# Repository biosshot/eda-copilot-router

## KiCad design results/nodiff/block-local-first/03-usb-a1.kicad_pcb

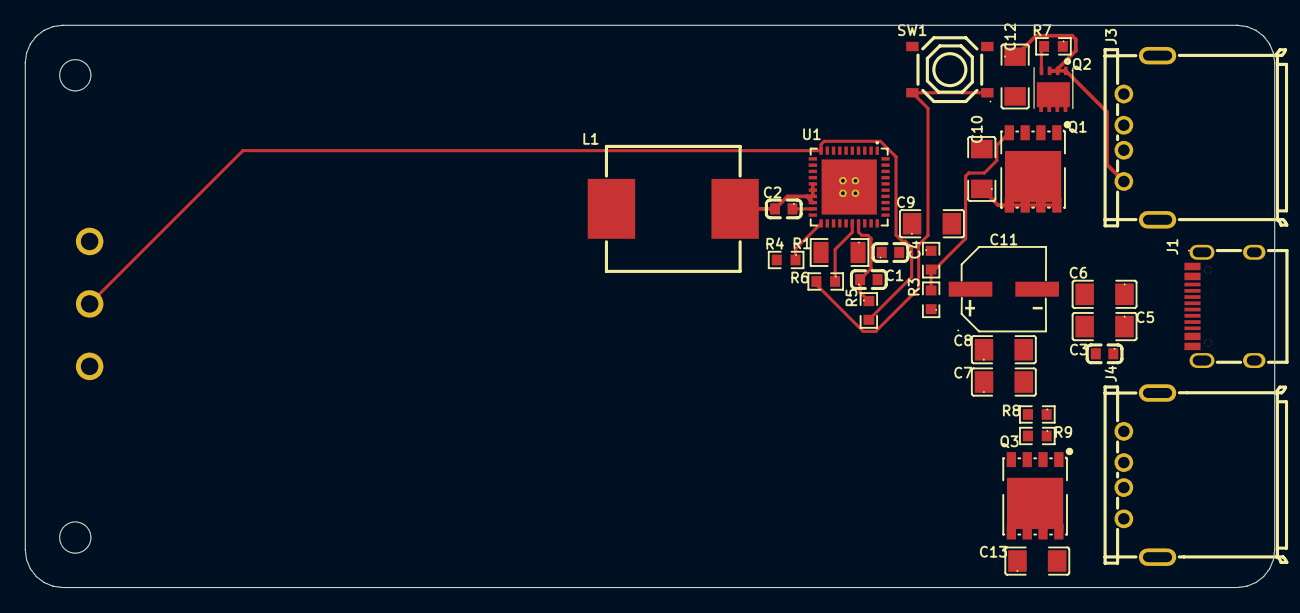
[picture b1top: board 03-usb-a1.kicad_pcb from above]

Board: 2 copper layers, 100.0 x 45.0 mm, 32 parts (1 on the bottom side), 28 nets.

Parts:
C1: 2.2uF; C23630_C0603
C2, C3, C4: 100nF; C14663_C0603
C5, C6, C7, C8, C9: 22uF; C12891_C1206
C10, C12, C13: 10uF; C14860_C1206
C11: 220uF; C51018389_CAP-SMD_BD6.3-L6.6-W6.6-LS7.3-FD_H7.7
J1: USB-C_PD_IN_OUT; C165948_USB-C_SMD-TYPE-C-31-M-12_1
J2: BATTERY_1S2P_10AH_PROTECTED_NTC; C474882_CONN-TH_3P-P5.00_KF301-5.0-3P
J3: USB-A_QC_OUT1; C599115_USB-TH_87520-0010BLF
J4: USB-A_QC_OUT2; C599115_USB-TH_87520-0010BLF
L1: 2.2uH; C6495562_IND-SMD_L10.7-W10.0
Q1, Q3: SI7149DP-T1-GE3; C553982_POWERPAK-SO-8_L5.9-W4.9-P1.27-LS6.2-BL
Q2: CSD17577Q3A; C201632_VSONP-8_L3.1-W3.1-P0.65-LS3.5-BL
R1: 10mOhm; C844894_R1206
R2, R6, R7, R8: 100R; C105588_R0603
R3, R9: 10k; C98220_R0603
R4: 110k; C137807_R0603
R5: 82k; C137678_R0603
SW1: POWER_KEY; C318884_SW-SMD_4P-L5.1-W5.1-P3.70-LS6.5-TL_H1.5
U1: IP5328P; C188809_QFN-40_L6.0-W6.0-P0.50-BL-EP

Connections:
BAT_NTC: J2.2, R5.2, U1.10
BAT_POS: C9.1, J2.1, L1.2, U1.28
GND: C1.2, C3.2, C4.2, C5.2, C6.2, C7.2, C8.2, C9.2, C10.2, C11.2, C12.2, C13.2, J1.1, J1.2, J1.3, J1.4, J1.A1B12, J1.B1A12, J2.3, J3.4, J3.5, J3.6, J4.4, J4.5, J4.6, R4.2, SW1.3, SW1.4, U1.29, U1.41
KEY_IC: R6.1, U1.26
unnamed: C2.2, L1.1, U1.14, U1.15, U1.16, U1.17, U1.18
unnamed: R6.2, SW1.1, SW1.2
unnamed: C2.1, U1.19
unnamed: R4.1, U1.21
USB_A1_DM: J3.2, U1.38
USB_A1_DP: J3.3, U1.39
USB_A1_VBUS: C12.1, J3.1, Q2.1, Q2.2, Q2.3, U1.37
USB_A2_DM: J4.2, U1.40
USB_A2_DP: J4.3, U1.1
USB_A2_VBUS: C13.1, J4.1, Q3.5, Q3.6, Q3.7, Q3.8, U1.34
USB_CC1: J1.A5, U1.2
USB_CC2: J1.B5, U1.3
USB_DM: J1.A7, J1.B7, U1.4
USB_DP: J1.A6, J1.B6, U1.5
USB_VBUS: C10.1, J1.A4B9, J1.B4A9, Q1.5, Q1.6, Q1.7, Q1.8, U1.32
VBUS_GATE: Q1.4, R2.2, R3.2
VBUS_GATE_IC: R2.1, U1.33
VOUT1_GATE: Q2.4, R7.2
VOUT1_GATE_IC: R7.1, U1.36
VOUT2_GATE: Q3.4, R8.2, R9.2
VOUT2_GATE_IC: R8.1, U1.35
VREG_3V1: C1.1, R5.1, U1.27
VSYS_CONV: C3.1, C5.1, C6.1, C7.1, C8.1, C11.1, R1.1, U1.8, U1.9, U1.22, U1.23, U1.24
VSYS_PORT: C4.1, Q1.1, Q1.2, Q1.3, Q2.5, Q2.6, Q2.7, Q2.8, Q2.9, Q3.1, Q3.2, Q3.3, R1.2, R3.1, R9.1, U1.25
